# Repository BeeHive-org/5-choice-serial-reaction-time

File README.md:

# Serial Reaction Chamber

The chamber can be used to observe small rodents response to light stimulus. 

It has holes with a light on one end and a feeding slot with a light in the opposite end. Depending on the behavoiur being experimented the animal needs to poke it's nose into the correct hole and feeding occurs in accordance to the experiemntal rules.

 Its an implementation of a complete behavioural box using BeeHive, off the shelf components and 3D printed parts.
  
---

### Hardware:
- The supporting hardware for the project:
     * food_dispencer
    * reaction_chamber 
- Running on the Beehive platform under:
     + Electronics 

### Software:
-    The beehive platform uses ESP32 which can run either micropython or C++. 
-     testcode is provided in microPython.
 -   You can also use Bonsai for data collection on PC however this implimentation is not covered under this documentation.

If you wish to build the complete box please look at the [Overal BOM]{BOM} otherwise you can find indvidual sectional Bill of materials under each tab.

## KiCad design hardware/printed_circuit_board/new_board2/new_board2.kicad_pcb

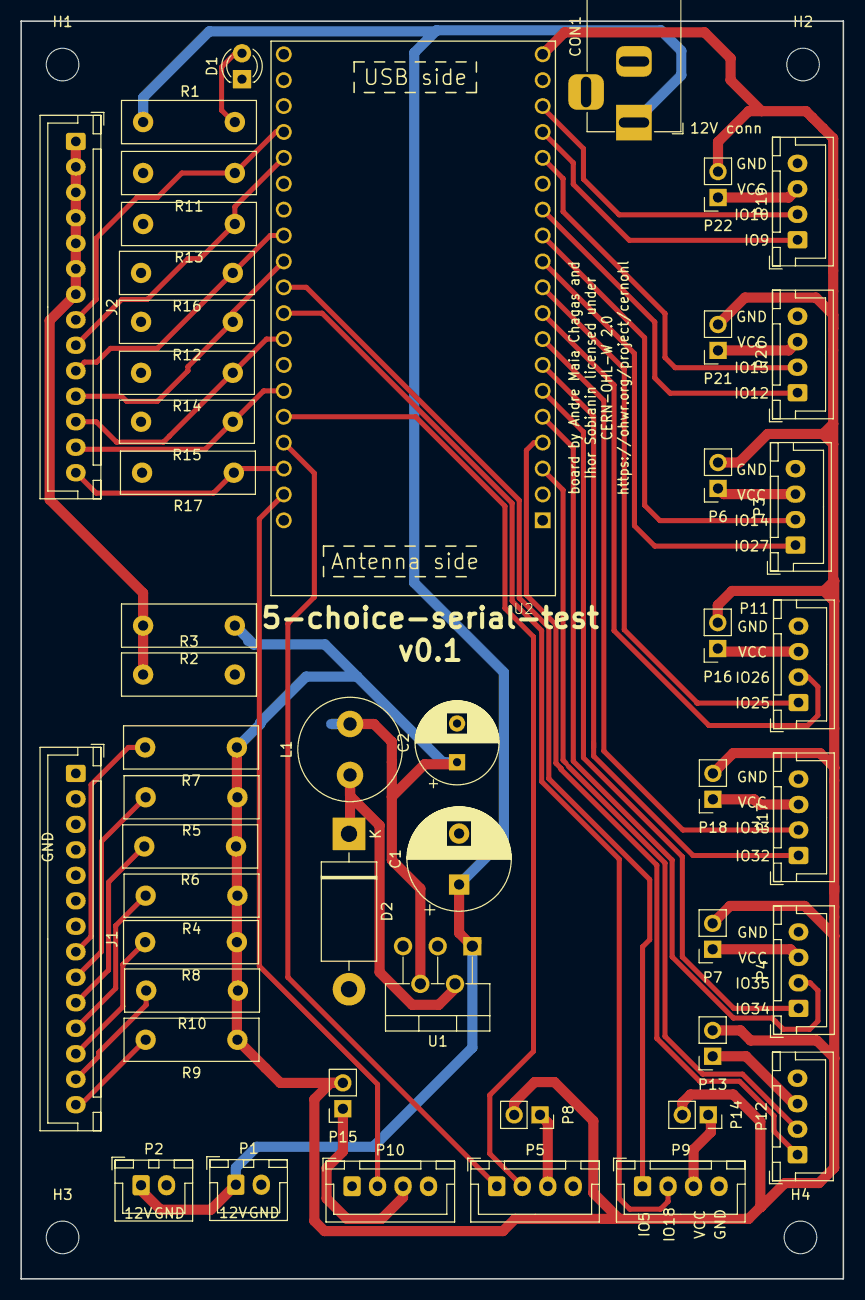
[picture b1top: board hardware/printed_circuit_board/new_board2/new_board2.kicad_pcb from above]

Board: 2 copper layers, 80.7 x 123.4 mm, 53 parts (0 on the bottom side), 49 nets.

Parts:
C1: 680µ; CP_Radial_D10.0mm_P5.00mm
C2: 220µ; CP_Radial_D8.0mm_P3.80mm
CON1: BARREL_JACK; BarrelJack_Horizontal
D1: LED; LED_D3.0mm
D2: Schottky 5A; D_DO-201AD_P15.24mm_Horizontal
H1, H2, H3, H4: MountingHole; MountingHole_3.2mm_M3
J1, J2: Conn_01x14_Socket; JST_XH_B14B-XH-A_1x14_P2.50mm_Vertical
L1: 33µH; L_Radial_D10.0mm_P5.00mm_Fastron_07M
P1, P2: Conn_01x02; JST_XH_B2B-XH-A_1x02_P2.50mm_Vertical
P3: D7; JST_XH_B4B-XH-A_1x04_P2.50mm_Vertical
P4: A1; JST_XH_B4B-XH-A_1x04_P2.50mm_Vertical
P5: UART; JST_XH_B4B-XH-A_1x04_P2.50mm_Vertical
P6, P7, P8, P13, P14, P15, P16, P18, P21, P22: Conn_01x02; PinSocket_1x02_P2.54mm_Vertical
P9: D4; JST_XH_B4B-XH-A_1x04_P2.50mm_Vertical
P10: D6; JST_XH_B4B-XH-A_1x04_P2.50mm_Vertical
P11: D8; JST_XH_B4B-XH-A_1x04_P2.50mm_Vertical
P12: A2; JST_XH_B4B-XH-A_1x04_P2.50mm_Vertical
P17: A3; JST_XH_B4B-XH-A_1x04_P2.50mm_Vertical
P19: I2C 1; JST_XH_B4B-XH-A_1x04_P2.50mm_Vertical
P20: I2C 2; JST_XH_B4B-XH-A_1x04_P2.50mm_Vertical
R1, R2: 560; R_Box_L13.0mm_W4.0mm_P9.00mm
R3: 1k; R_Box_L13.0mm_W4.0mm_P9.00mm
R4, R5, R6, R7, R8, R9, R10: 47; R_Box_L13.0mm_W4.0mm_P9.00mm
R11, R12, R13, R14, R15, R16, R17: 10k; R_Box_L13.0mm_W4.0mm_P9.00mm
U1: LM2596T-5; TO-220-5_P3.4x3.7mm_StaggerOdd_Lead3.8mm_Vertical
U2: ESP32-DEVKITC-32D; MODULE_ESP32-DEVKITC-32D

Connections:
+3V3: J2.1, J2.2, J2.3, J2.4, J2.5, J2.6, J2.7, R2.2, R3.1
+5V: C2.1, L1.2, P6.2, P7.2, P8.2, P13.2, P14.2, P15.2, P16.2, P18.2, P21.2, P22.2, R2.1, R4.1, R5.1, R6.1, R7.1, R8.1, R9.1, R10.1, U1.4 (FB), U2.19 (EXT_5V)
+12V: C1.1, CON1.1, P1.1, P2.1, R1.2, U1.1 (VIN)
A1-3: P4.1, U2.6 (IO35)
A1-4: P4.2, U2.5 (IO34)
A2-3: P12.1, U2.4 (SENSOR_VN)
A2-4: P12.2, U2.3 (SENSOR_VP)
A3-3: P17.1, U2.7 (IO32)
A3-4: P17.2, U2.8 (IO33)
D1-3: J2.8, R11.1, U2.35 (IO15)
D1-4: J2.9, R13.1, U2.34 (IO2)
D3-3: J2.10, R16.1, U2.31 (IO16)
D3-4: J2.11, R12.1, U2.30 (IO17)
D4-3: P9.1, U2.29 (IO5)
D4-4: P9.2, U2.28 (IO18)
D5-3: J2.12, R14.1, U2.27 (IO19)
D5-4: J2.13, R15.1, U2.25 (IO21)
D6-3: J2.14, R17.1, U2.22 (IO22)
D6-4: P10.2, U2.21 (IO23)
D7-3: P3.1, U2.12 (IO14)
D7-4: P3.2, U2.11 (IO27)
D8-3: P11.1, U2.10 (IO26)
D8-4: P11.2, U2.9 (IO25)
GND: C1.2, C2.2, CON1.2, CON1.3, D1.1 (K), D2.2 (A), J1.1, J1.2, J1.3, J1.4, J1.5, J1.6, J1.7, P1.2, P2.2, P3.4, P4.4, P5.4, P9.4, P10.4, P11.4, P12.4, P17.4, P19.4, P20.4, R3.2, R11.2, R12.2, R13.2, R14.2, R15.2, R16.2, R17.2, U1.3 (GND), U1.5 (~ON/OFF), U2.14 (GND1), U2.20 (GND3), U2.26 (GND2)
I2C_1-3: P19.1, U2.16 (SD2)
I2C_1-4: P19.2, U2.17 (SD3)
I2C_2-3: P20.1, U2.13 (IO12)
I2C_2-4: P20.2, U2.15 (IO13)
unnamed: D1.2 (A), R1.1
unnamed: D2.1 (K), L1.1, U1.2 (OUT)
unnamed: J1.8, R7.2
unnamed: J1.9, R5.2
unnamed: J1.10, R6.2
unnamed: J1.11, R4.2
unnamed: J1.12, R8.2
unnamed: J1.13, R10.2
unnamed: J1.14, R9.2
unnamed: P3.3, P6.1
unnamed: P4.3, P7.1
unnamed: P5.3, P8.1
unnamed: P10.3, P15.1
unnamed: P11.3, P16.1
unnamed: P12.3, P13.1
unnamed: P9.3, P14.1
unnamed: P17.3, P18.1
unnamed: P19.3, P22.1
unnamed: P20.3, P21.1
RX: P5.2, U2.24 (RXD0)
TX: P5.1, U2.23 (TXD0)

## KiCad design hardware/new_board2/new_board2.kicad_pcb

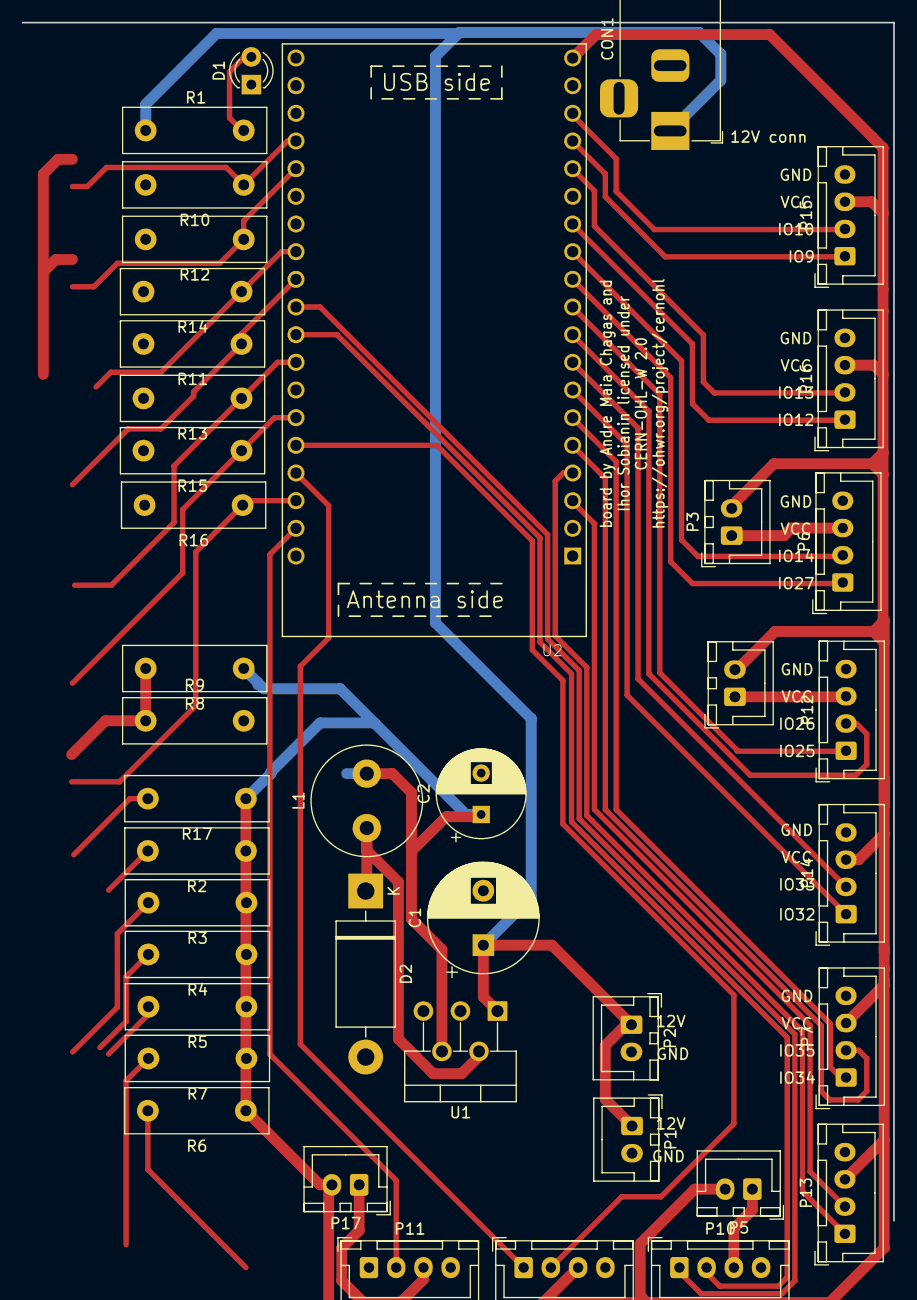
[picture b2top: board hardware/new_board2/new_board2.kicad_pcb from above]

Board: 2 copper layers, 80.0 x 110.0 mm, 41 parts (0 on the bottom side), 36 nets.

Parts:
C1: 680µ; CP_Radial_D10.0mm_P5.00mm
C2: 220µ; CP_Radial_D8.0mm_P3.80mm
CON1: BARREL_JACK; BarrelJack_Horizontal
D1: LED; LED_D3.0mm
D2: Schottky 5A; D_DO-201AD_P15.24mm_Horizontal
L1: 33µH; L_Radial_D10.0mm_P5.00mm_Fastron_07M
P1, P2, P3, P5, P17, P18: Conn_01x02; JST_XH_B2B-XH-A_1x02_P2.50mm_Vertical
P6: D7; JST_XH_B4B-XH-A_1x04_P2.50mm_Vertical
P7: A1; JST_XH_B4B-XH-A_1x04_P2.50mm_Vertical
P8: UART; JST_XH_B4B-XH-A_1x04_P2.50mm_Vertical
P10: D4; JST_XH_B4B-XH-A_1x04_P2.50mm_Vertical
P11: D6; JST_XH_B4B-XH-A_1x04_P2.50mm_Vertical
P12: D8; JST_XH_B4B-XH-A_1x04_P2.50mm_Vertical
P13: A2; JST_XH_B4B-XH-A_1x04_P2.50mm_Vertical
P14: A3; JST_XH_B4B-XH-A_1x04_P2.50mm_Vertical
P15: I2C 1; JST_XH_B4B-XH-A_1x04_P2.50mm_Vertical
P16: I2C 2; JST_XH_B4B-XH-A_1x04_P2.50mm_Vertical
R1, R8: 560; R_Box_L13.0mm_W4.0mm_P9.00mm
R2, R3, R4, R5, R6, R7, R17: 47; R_Box_L13.0mm_W4.0mm_P9.00mm
R9: 1k; R_Box_L13.0mm_W4.0mm_P9.00mm
R10, R11, R12, R13, R14, R15, R16: 10k; R_Box_L13.0mm_W4.0mm_P9.00mm
U1: LM2596T-5; TO-220-5_P3.4x3.7mm_StaggerOdd_Lead3.8mm_Vertical
U2: ESP32-DEVKITC-32D; MODULE_ESP32-DEVKITC-32D

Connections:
+3V3: R8.2, R9.1
+5V: C2.1, L1.2, P3.2, P5.2, P7.3, P8.3, P13.3, P14.3, P15.3, P16.3, P17.2, P18.2, R2.1, R3.1, R4.1, R5.1, R6.1, R7.1, R8.1, R17.1, U1.4 (FB), U2.19 (EXT_5V)
A1-3: P7.1, U2.6 (IO35)
A1-4: P7.2, U2.5 (IO34)
A2-3: P13.1, U2.4 (SENSOR_VN)
A2-4: P13.2, U2.3 (SENSOR_VP)
A3-3: P14.1, U2.7 (IO32)
A3-4: P14.2, U2.8 (IO33)
D1-3: R10.1, U2.35 (IO15)
D1-4: R12.1, U2.34 (IO2)
D3-3: R14.1, U2.31 (IO16)
D3-4: R11.1, U2.30 (IO17)
D4-3: P10.1, U2.29 (IO5)
D4-4: P10.2, U2.28 (IO18)
D5-3: R13.1, U2.27 (IO19)
D5-4: R15.1, U2.25 (IO21)
D6-3: R16.1, U2.22 (IO22)
D6-4: P11.2, U2.21 (IO23)
D7-3: P6.1, U2.12 (IO14)
D7-4: P6.2, U2.11 (IO27)
D8-3: P12.1, U2.10 (IO26)
D8-4: P12.2, U2.9 (IO25)
GND: C1.2, C2.2, CON1.2, CON1.3, D1.1 (K), D2.2 (A), P1.2, P2.2, P6.4, P7.4, P8.4, P10.4, P11.4, P12.4, P13.4, P14.4, P15.4, P16.4, R9.2, R10.2, R11.2, R12.2, R13.2, R14.2, R15.2, R16.2, U1.3 (GND), U1.5 (~ON/OFF), U2.14 (GND1), U2.20 (GND3), U2.26 (GND2)
I2C_1-3: P15.1, U2.16 (SD2)
I2C_1-4: P15.2, U2.17 (SD3)
I2C_2-3: P16.1, U2.13 (IO12)
I2C_2-4: P16.2, U2.15 (IO13)
unnamed: D1.2 (A), R1.1
unnamed: D2.1 (K), L1.1, U1.2 (OUT)
unnamed: C1.1, CON1.1, P1.1, P2.1, R1.2, U1.1 (VIN)
unnamed: P3.1, P6.3
unnamed: P5.1, P10.3
unnamed: P11.3, P17.1
unnamed: P12.3, P18.1
RX: P8.2, U2.24 (RXD0)
TX: P8.1, U2.23 (TXD0)

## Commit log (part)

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2022-11-10 add working code, solved by Dexter
2022-11-28 put together an adaptor for the food hopper
    quick and dirt adaptation from an existing OSH project to use our existing motors
2022-11-28 update hopper
2022-11-29 first working version?
2023-01-09 update 3d printed components
2023-01-18 work on designs
2023-01-19 update rotor
2023-01-19 rework food well
2023-01-19 work on 3D designs
2023-01-20 Python code to run 5CSRTT
2023-01-22 updated serial beehive
2023-01-24 5csrtt modifications
2023-02-10 code change 5CSRTT
2023-02-22 Update makerbeams
2023-02-22 perspex walls
2023-02-22 repo clean up nd some code clean up
2023-02-22 update code
2023-02-23 start building wifi commmunication system
2023-02-27 back panel
2023-02-27 small cleanups
2023-02-28 boards cables and updated 5-choice protocol
2023-03-02 curved_wall2
2023-03-02 Update boards_cables
2023-03-08 update some of the designs, simplify the work pipeline by calling modules, instead of rewriting them
2023-03-08 update nose poke wall so that it will protude inside cage
2023-03-08 update wall after printing
2023-03-13 add moving avergae code
2023-03-14 update code and some 3d designs
2023-03-14 correct spelling mistakes
2023-03-17 update curved walll design for two part printing
2023-03-29 update 3d designs
2023-04-04 update
    update
2023-04-27 updated serial beehive and outside1
2023-05-05 change backpanel and the size of the hole for the pellet dispenser shoot
2023-05-05 update backpanel to cover the entire backwall
2023-05-12 update designs
2023-05-12 fix bug with jumping the SDs in the SD training phase
2023-05-12 update code for outside.py
    remove redundancies, and useless for loops
2023-05-15 fix some bugs with phases 9 and 10.
2023-05-15 5-c training trial no changed
2023-05-21 Update outside
2023-07-24 new board dedicated for leds and light transistors
2023-07-24 update new board
2023-07-24 more updates
2023-07-24 pcb version 0.1
2023-07-24 update board
2023-08-04 add first version of new board
2023-10-24 update food dispenser
2023-10-24 create dedicated main board
2023-10-24 create some software backups
2023-11-02 update base
2023-11-02 update gitgnore and cleanup 3d files
2023-11-03 update food hopper
2023-11-13 update printed parts
2023-11-18 clean up repo and make cap for food dispenser
2023-11-18 clean up
2023-11-18 improve lid
2023-11-21 add backpanel
2023-11-21 add missing stls
2023-11-30 clean up repo
2023-11-30 update lid (non-critical)
2023-12-15 new rotor design
    Updated the rotor design to accurately fits the measurements of the dispenser lid.
    Moved the previous version (.fcstd, .stl) to archive folder
2024-01-18 create code to test the servo and IR beams
2024-02-05 mount with chute new versions
    Uploaded FreeCad and STL files of new versions of pellet dispenser part (Mount with chute versions 2-6)
2024-06-13 clean up dsstore icloud files
2024-09-11 Documentation and html site
2024-09-11 added _site folder
2024-09-11 added worlflows
2024-09-19 Documentation update
2024-09-19 reorganise location of files and fix small typo mistakes
2024-09-19 render site
2024-09-19 fix typo
2024-09-20 documantation update
2024-09-20 _site updated
2024-09-20 removed _build
2024-09-23 Improved on documentation
2024-09-30 Production cost added
2024-09-30 link to read me png added
2024-09-30 read me updated
2024-09-30 read me picture link added
2024-12-10 upadted ecase_rnl
2025-02-11 add pellet dispenser as submodule, rename schematics to printed circuit board, fix typos
2025-02-13 clean up code and move reward system from stepper to servo motor
2025-02-20 fix small bugs related to elif statements not being properly set
2025-03-26 change gitignore to remove environment folder
2025-03-26 remove bug where variable was called before being assigned
2025-03-27 edited feeding wall and lid
2025-05-08 update ports to match sarahs box in Japan
2025-05-30 updated version of the code, with checks on the magazine training, and saving data after each trial
2025-06-10 change pins for sensors and fix magazine training
2025-06-10 simplify PCB, making stable connections for LEDs using a ULN2003, remove jumpers, THIS IS STILL UNTESTED!
2025-06-10 change variables names to something more explicit: 'buttons' are now sensors, etc
2025-06-10 fix bug in setting up box where was being called for some instances, instead of
2025-06-23 add thonny image, update outside and serial_beehive
2025-06-27 one more pass at the pcb

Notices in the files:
hardware/new_board2/new_board2.kicad_pcb:
board by Andre Maia Chagas and
Ihor Sobianin licensed under
CERN-OHL-W 2.0
